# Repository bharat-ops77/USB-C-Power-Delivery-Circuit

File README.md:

#  • USB-C-Power-Delivery-Circuit
A custom hardware and firmware solution for negotiating Power Delivery (PD) contracts from USB-C sources. This project utilizes an Arduino-compatible microcontroller alongside the FUSB302B USB Type-C controller to request specific voltage and current profiles from a compatible USB-C charger.

# • Repository Structure

```
usb-c-pd-trigger/
├── Firmware/
│   ├── usb-c-demo.ino             # Main Arduino sketch
│   ├── FUSB302.c / FUSB302.h      # FUSB302B chip driver
│   ├── tcpm_driver.cpp / .h       # Hardware I2C wrapper
│   ├── usb_pd_policy.c            # USB PD policy engine
│   ├── usb_pd_protocol.c          # USB PD state machine
│   ├── usb_pd_driver.c / .h       # Sink capabilities and board definitions
│   ├── usb_pd.h                   # Core PD protocol definitions
│   └── usb_pd_tcpm.h              # Type-C Port Manager interface
├── Hardware/
│   ├── Schematics/                # PDF schematics of the trigger board
│   ├── Gerbers/                   # ZIP file containing Gerber files for PCB fabrication
│   └── Source/                    # KiCad project files
├── Docs/
│   ├── images/                    # High-resolution photos of the populated board
│   └── datasheets/                #  FUSB
├── LICENSE                        # GNU License
└── README.md                      # Project documentation (Template below)
```

##  • Features 
###  • FUSB302B TCPC Integration: 
 • Full Type-C Port Controller implementation over I2C.   
 • Dynamic Voltage Switching: Cycle through available Power Data Objects (PDOs) offered by the charger using a physical pushbutton.  
 • Status Indicators: Onboard LED provides visual feedback for state changes and debugging.  
 • Customizable Sink Capabilities: Default sink profiles request 5V, 9V, and 20V at 500mA, with the driver supporting configurations up to 60W (12V       max operating, 5A peak). 
##  • Schematic 

# • Hardware Specifications
## Pin Mapping
### The firmware expects the following pin connections to the microcontroller:

## • System Limits
The safety boundaries defined in the firmware (usb_pd_driver.h) are:
Maximum Power: 60 W   
Maximum Current: 5 A   
Maximum Voltage: 12 V

## • Firmware Architecture
The firmware acts as a USB-C PD Sink (UFP). It is divided into three primary layers:   
### • TCPM (Type-C Port Manager):
Handles the I2C communication with the FUSB302B, pushing physical layer resets, managing the RX/TX FIFOs, and measuring CC pin states.   
### • PD Protocol Layer:
A state machine (usb_pd_protocol.c) that handles message transmission, GoodCRC acknowledgments, Hard/Soft resets, and contract negotiations.
### • PD Policy Engine: 
Determines which voltages to accept and request based on the capabilities advertised by the source charger (usb_pd_policy.c)

## • Getting Started
### • Prerequisites
 1. Arduino IDE (or PlatformIO).
 2. An ESP8266, ESP32, or similar Arduino-compatible board containing D3, D4, and D5 pins.
 ### • Installation & Flashing
 1. Clone this repository to your local machine.
 2. Open Firmware/usb-c-pd-trigger.ino in your Arduino IDE.   
 3. Ensure the Wire library is available for your target board.
 4. Compile and upload the firmware to your microcontroller.

 ## • Usage
 1. Connect the board to a USB-C PD power supply.
 2. The state machine will initialize in PD_STATE_SNK_DISCONNECTED and automatically negotiate the first available voltage contract (usually 5V).     3. Press the pushbutton (D4): The trigger board will initiate a soft reset. Upon recovering the connection, it steps to the next available source   capability index.   
 4. Observe the LED (D5): The LED state toggles on each successful button press to confirm the interaction.
 ## • Connection Diagram

## • Designed PCB
<table>
  <tr>
    <th>First Layer</th>
    <th>Second Layer</th>
  </tr>
  <tr>
    <td>
</td>
    <td>
</td>
  </tr>
</table>

## • Rendered PCB (Without Components)
<table>
  <tr>
    <th>First Layer</th>
    <th>Second Layer</th>
  </tr>
  <tr>
    <td>
  </td>
    <td>

</td>
  </tr>
</table>

## • 3D Model (With Components)

#### • Feel absolutely free to suggest better architecture or board layouts , download or fabricate the PCB and create your own project files using this repo.

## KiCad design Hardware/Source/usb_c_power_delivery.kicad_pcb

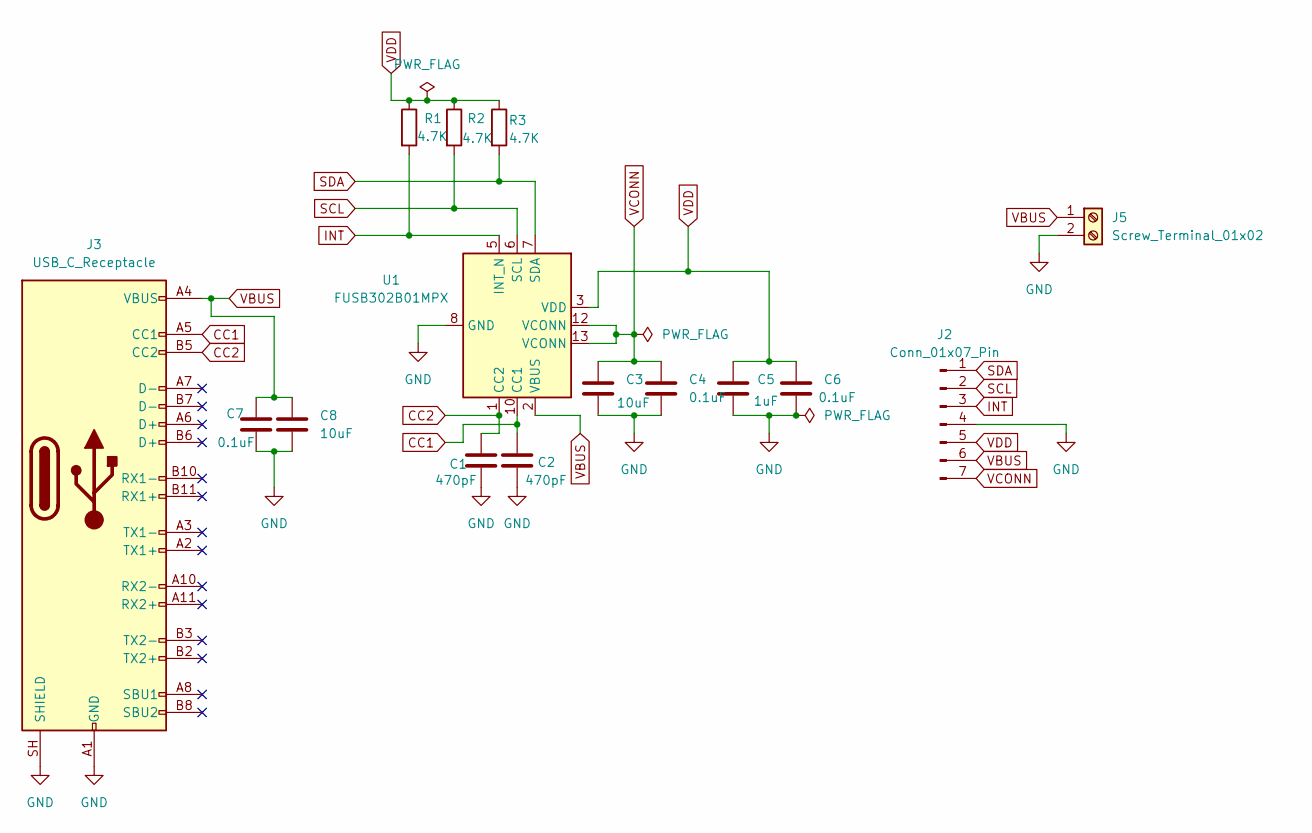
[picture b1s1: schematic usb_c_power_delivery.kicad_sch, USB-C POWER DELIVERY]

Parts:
C1, C2: 470pF; C_Disc_D3.0mm_W1.6mm_P2.50mm
C3, C8: 10uF; C_1206_3216Metric
C4, C6, C7: 0.1uF; C_0402_1005Metric
C5: 1uF; C_0603_1608Metric
J2: Conn_01x07_Pin; TerminalBlock_4Ucon_1x07_P3.50mm_Horizontal
J3: USB_C_Receptacle; USB_C_Receptacle_XKB_U262-16XN-4BVC11
J5: Screw_Terminal_01x02; TerminalBlock_MaiXu_MX126-5.0-02P_1x02_P5.00mm
R1, R2, R3: 4.7K; R_0603_1608Metric
U1: FUSB302B01MPX; WQFN-14-1EP_2.5x2.5mm_P0.5mm_EP1.45x1.45mm

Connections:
CC1: C2.1, J3.A5 (CC1), U1.10 (CC1), U1.11 (CC1)
CC2: C1.1, J3.B5 (CC2), U1.1 (CC2), U1.14 (CC2)
GND: C1.2, C2.2, C3.2, C4.2, C5.2, C6.2, C7.2, C8.2, J2.4, J3.A1 (GND), J3.A12 (GND), J3.B1 (GND), J3.B12 (GND), J3.SH (SHIELD), J5.2, U1.8 (GND), U1.9 (GND), U1.15 (GND)
INT: J2.3, R1.2, U1.5 (INT_N)
SCL: J2.2, R2.2, U1.6 (SCL)
SDA: J2.1, R3.2, U1.7 (SDA)
VBUS: C7.1, C8.1, J2.6, J3.A4 (VBUS), J3.A9 (VBUS), J3.B4 (VBUS), J3.B9 (VBUS), J5.1, U1.2 (VBUS)
VCONN: C3.1, C4.1, J2.7, U1.12 (VCONN), U1.13 (VCONN)
VDD: C5.1, C6.1, J2.5, R1.1, R2.1, R3.1, U1.3 (VDD), U1.4 (VDD)

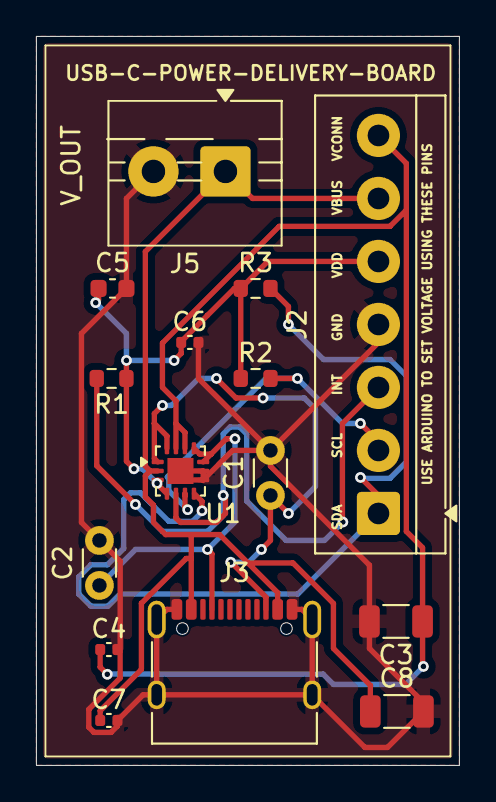
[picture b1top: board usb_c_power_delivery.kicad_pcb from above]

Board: 2 copper layers, 23.5 x 40.5 mm, 15 parts (0 on the bottom side), 9 nets.
